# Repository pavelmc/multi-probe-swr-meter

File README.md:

# Multi-Probe SWR/PWR Meter with Icom Tuner handling for Yaesu Rigs #

## Icom Tuner handling for Yaesu Rigs ##

This hardware implements a way to handle the following Icom tuners:

* AT-130(E) (same as AH-3)
* AT-140 (same as AH-4)

## The software ##

The software is made in JAL & Jallib, please visit http://www.justanotherlanguage.com

The hex is ready for a PIC16F887 with a cheap motherboard crystal of 14.31818 Mhz

## Comments, contributions and questions ##

If is issues about the software or kicad files use the ISSUES tab on this page, all other infos via the author email at pavelmc@gmail.com

## Changelog ##

### v0.1 ###

* Initial creation of the repository.
* Just the first PCB, the main one, other will follow.
* We use only one Sided PCB, so all vias to the other side are in deed wires

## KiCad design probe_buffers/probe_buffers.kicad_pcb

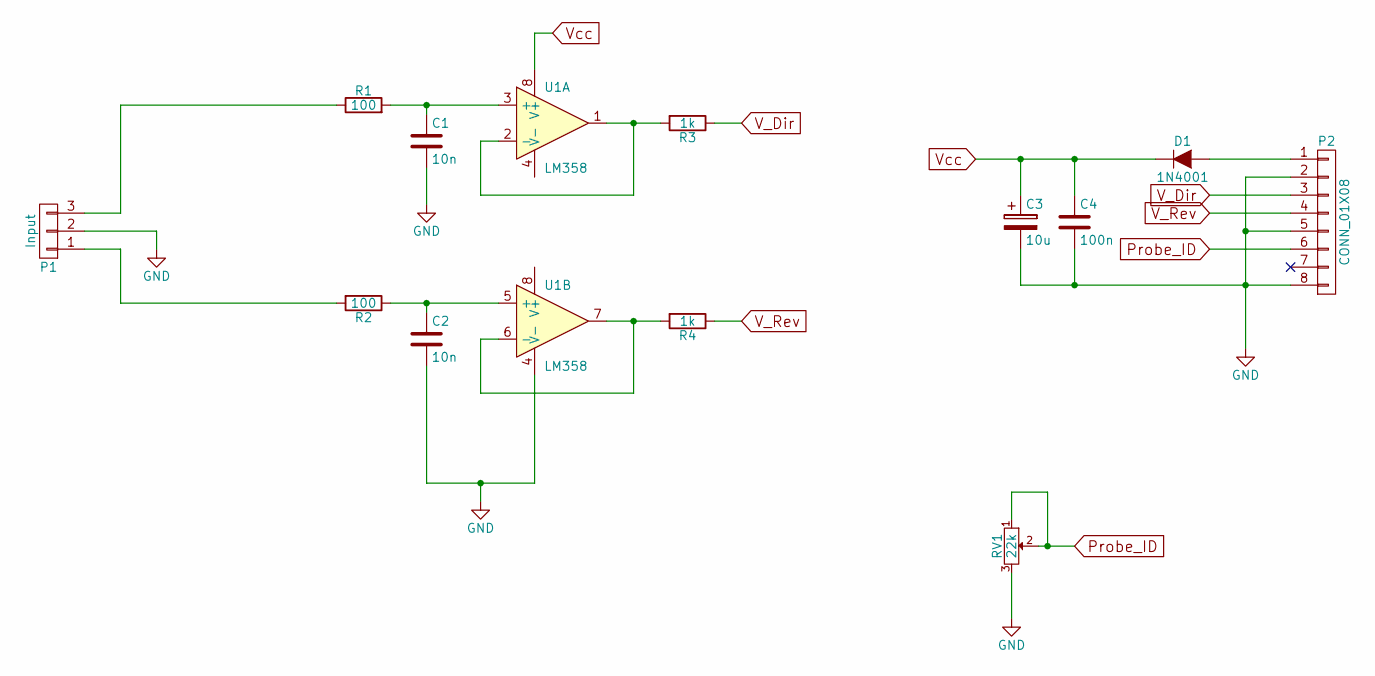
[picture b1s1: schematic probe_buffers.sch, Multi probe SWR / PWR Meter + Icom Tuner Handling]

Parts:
C1, C2: 10n; C_Disc_D6_P5
C3: 10u; C_Disc_D7.5_P5
C4: 100n; C_Disc_D6_P5
D1: 1N4001; Diode_DO-41_SOD81_Vertical_KathodeUp
P1: Input; Pin_Header_Straight_1x03
P2: CONN_01X08; Pin_Header_Straight_1x08
R1, R2: 100; Resistor_Horizontal_RM10mm
R3, R4: 1k; Resistor_Horizontal_RM10mm
RV1: 22k; Potentiometer_Bourns_3296W_3-8Zoll_Inline_ScrewUp
U1: LM358; SOIC-8_3.9x4.9mm_Pitch1.27mm

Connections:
GND: C1.2, C2.2, C3.2, C4.2, P1.2, P2.2, P2.5, P2.8, RV1.3, U1.4 (V-)
unnamed: C1.1, R1.2, U1.3 (+)
unnamed: C2.1, R2.1, U1.5 (+)
unnamed: D1.2 (A), P2.1
unnamed: P1.1, R2.2
unnamed: P1.3, R1.1
unnamed: R3.2, U1.1, U1.2 (-)
unnamed: R4.2, U1.6 (-), U1.7
Probe_ID: P2.6, RV1.1, RV1.2
V_Dir: P2.3, R3.1
V_Rev: P2.4, R4.1
Vcc: C3.1, C4.1, D1.1 (K), U1.8 (V+)

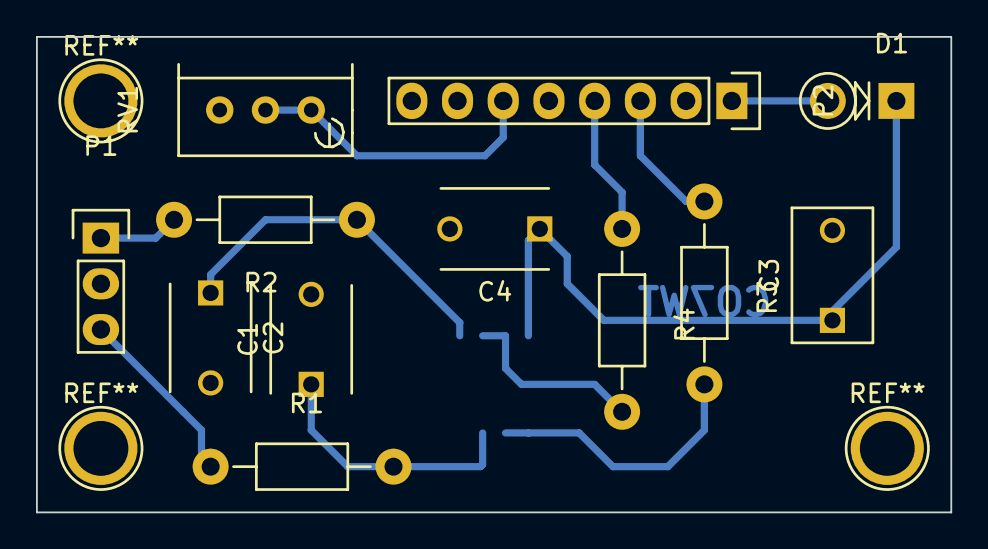
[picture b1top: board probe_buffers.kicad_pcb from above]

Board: 2 copper layers, 50.8 x 26.4 mm, 13 parts (1 on the bottom side), 12 nets.

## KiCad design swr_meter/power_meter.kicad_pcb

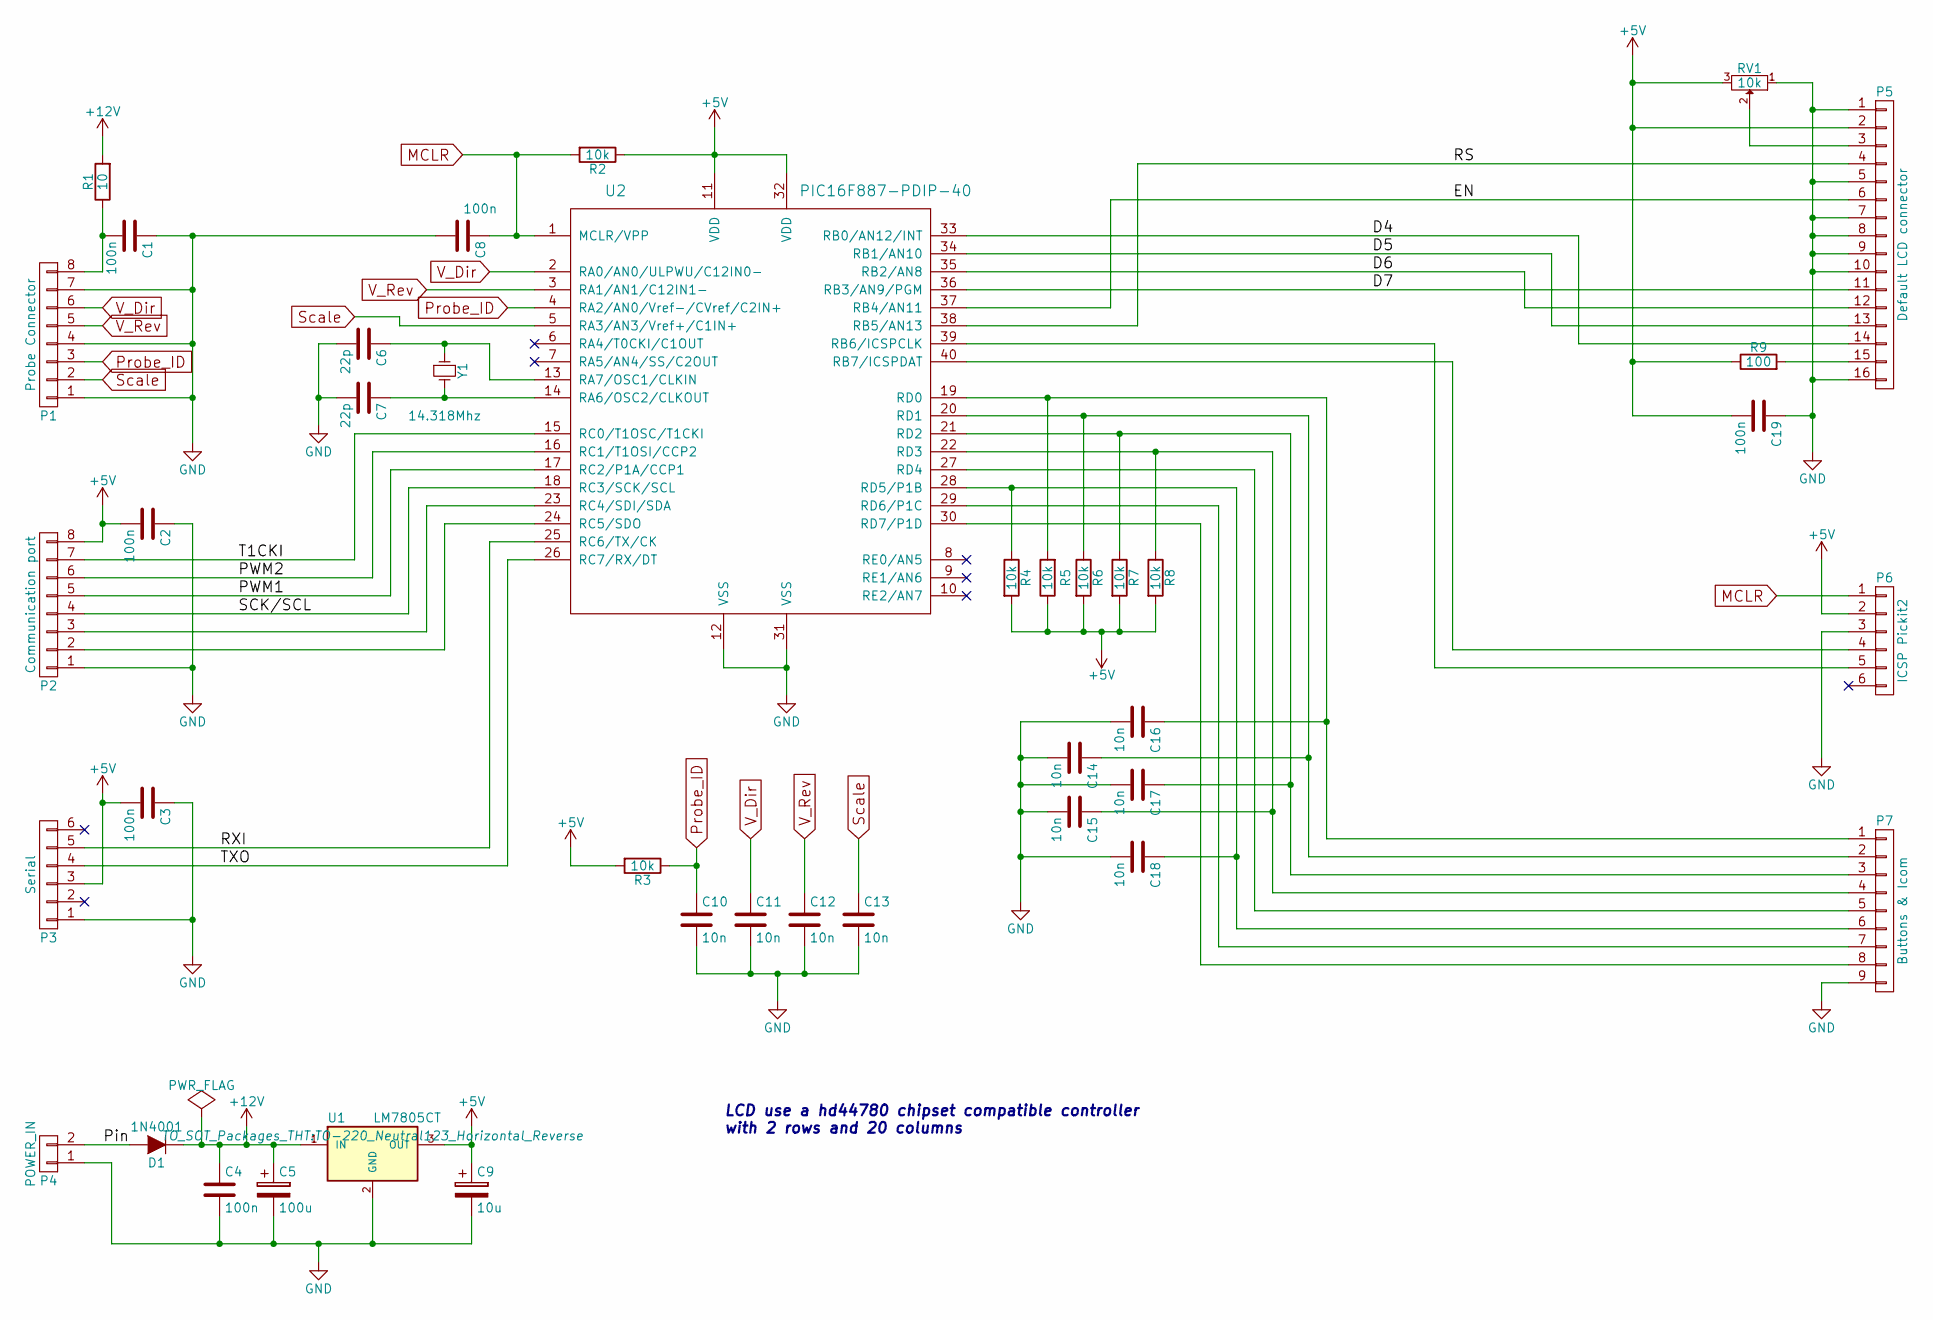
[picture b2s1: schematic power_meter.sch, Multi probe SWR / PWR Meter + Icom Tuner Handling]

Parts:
C1, C2, C3, C4, C8, C19: 100n; C_Disc_D6_P5
C5: 100u; C_Disc_D7.5_P5
C6, C7: 22p; C_Disc_D6_P5
C9: 10u; C_Disc_D7.5_P5
C10, C11, C12, C13, C14, C15, C16, C17, C18: 10n; C_Disc_D6_P5
D1: 1N4001; Diode_DO-41_SOD81_Vertical_KathodeUp
P1: Probe Connector; Pin_Header_Straight_1x08
P2: Communication port; Pin_Header_Straight_1x08
P3: Serial; Pin_Header_Straight_1x06
P4: POWER_IN; Pin_Header_Straight_1x02
P5: Default LCD connector; Pin_Header_Straight_1x16
P6: ICSP Pickit2; Pin_Header_Straight_1x06
P7: Buttons & Icom; Pin_Header_Straight_1x09
R1: 10; Resistor_Horizontal_RM10mm
R2, R3, R4, R5, R6, R7, R8: 10k; Resistor_Horizontal_RM10mm
R9: 100; Resistor_Horizontal_RM10mm
RV1: 10k; Pin_Header_Straight_1x03
U1: LM7805CT; TO-220_Neutral123_Horizontal_Reverse
U2: PIC16F887-PDIP-40; DIP-40_W15.24mm_LongPads
Y1: 14.318Mhz; Crystal_HC49-U_Vertical

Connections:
+5V: C2.2, C3.2, C9.1, C19.2, P2.8, P3.3, P5.2, P6.2, R2.1, R3.2, R4.2, R5.1, R6.2, R7.2, R8.2, R9.1, RV1.3, U1.3 (OUT), U2.11 (VDD), U2.32 (VDD)
+12V: C4.1, C5.1, D1.1 (K), R1.2, U1.1 (IN)
/D4: P5.14, U2.33 (RB0/AN12/INT)
/D5: P5.13, U2.34 (RB1/AN10)
/D6: P5.12, U2.35 (RB2/AN8)
/D7: P5.11, U2.36 (RB3/AN9/PGM)
/EN: P5.6, U2.37 (RB4/AN11)
/PWM1: P2.5, U2.17 (RC2/P1A/CCP1)
/PWM2: P2.6, U2.16 (RC1/T1OSI/CCP2)
/Pin: D1.2 (A), P4.2
/RS: P5.4, U2.38 (RB5/AN13)
/RXI: P3.5, U2.25 (RC6/TX/CK)
/SCK/SCL: P2.4, U2.18 (RC3/SCK/SCL)
/SDI/SDA: P2.3, U2.23 (RC4/SDI/SDA)
/SDO: P2.2, U2.24 (RC5/SDO)
/T1CKI: P2.7, U2.15 (RC0/T1OSC/T1CKI)
/TXO: P3.4, U2.26 (RC7/RX/DT)
GND: C1.1, C2.1, C3.1, C4.2, C5.2, C6.2, C7.2, C8.2, C9.2, C10.2, C11.2, C12.2, C13.2, C14.2, C15.2, C16.2, C17.2, C18.2, C19.1, P1.1, P1.4, P1.7, P2.1, P3.1, P4.1, P5.1, P5.5, P5.7, P5.8, P5.9, P5.10, P5.16, P6.3, P7.9, RV1.1, U1.2 (GND), U2.12 (VSS), U2.31 (VSS)
MCLR: C8.1, P6.1, R2.2, U2.1 (MCLR/VPP)
unnamed: C1.2, P1.8, R1.1
unnamed: C6.1, U2.13 (RA7/OSC1/CLKIN), Y1.1
unnamed: C7.1, U2.14 (RA6/OSC2/CLKOUT), Y1.2
unnamed: C14.1, P7.2, R6.1, U2.20 (RD1)
unnamed: C15.1, P7.4, R8.1, U2.22 (RD3)
unnamed: C16.1, P7.1, R5.2, U2.19 (RD0)
unnamed: C17.1, P7.3, R7.1, U2.21 (RD2)
unnamed: C18.1, P7.6, R4.1, U2.28 (RD5/P1B)
unnamed: P5.3, RV1.2
unnamed: P5.15, R9.2
unnamed: P6.4, U2.40 (RB7/ICSPDAT)
unnamed: P6.5, U2.39 (RB6/ICSPCLK)
unnamed: P7.5, U2.27 (RD4)
unnamed: P7.7, U2.29 (RD6/P1C)
unnamed: P7.8, U2.30 (RD7/P1D)
Probe_ID: C10.1, P1.3, R3.1, U2.4 (RA2/AN0/Vref-/CVref/C2IN+)
Scale: C13.1, P1.2, U2.5 (RA3/AN3/Vref+/C1IN+)
V_Dir: C11.1, P1.6, U2.2 (RA0/AN0/ULPWU/C12IN0-)
V_Rev: C12.1, P1.5, U2.3 (RA1/AN1/C12IN1-)

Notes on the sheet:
LCD use a hd44780 chipset compatible controller with 2 rows and 20 columns

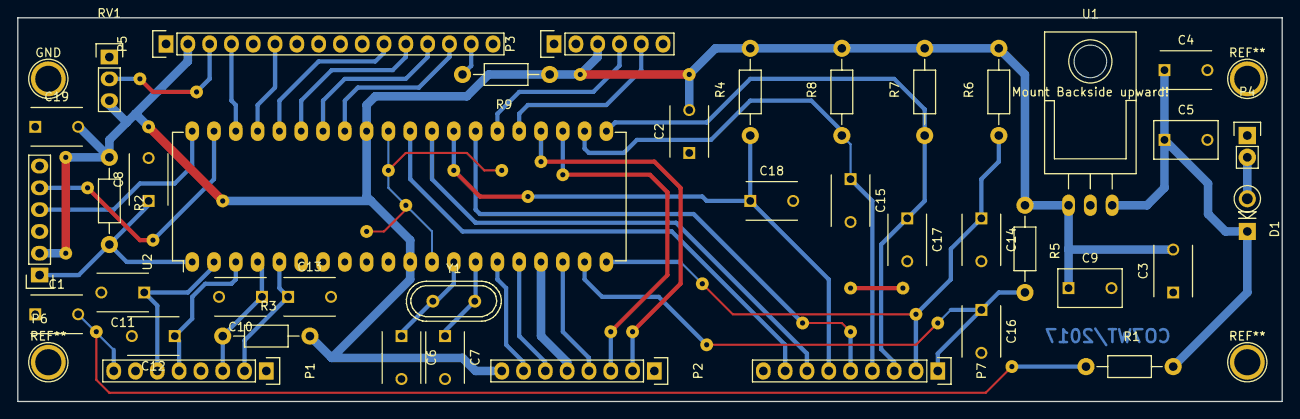
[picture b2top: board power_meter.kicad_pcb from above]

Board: 2 copper layers, 147.3 x 44.7 mm, 41 parts (0 on the bottom side), 38 nets.

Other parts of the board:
GND: 1pin

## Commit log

2017-08-29 Start
2017-08-30 Change in folders distribution
2017-08-30 Add more temp files to exclude
